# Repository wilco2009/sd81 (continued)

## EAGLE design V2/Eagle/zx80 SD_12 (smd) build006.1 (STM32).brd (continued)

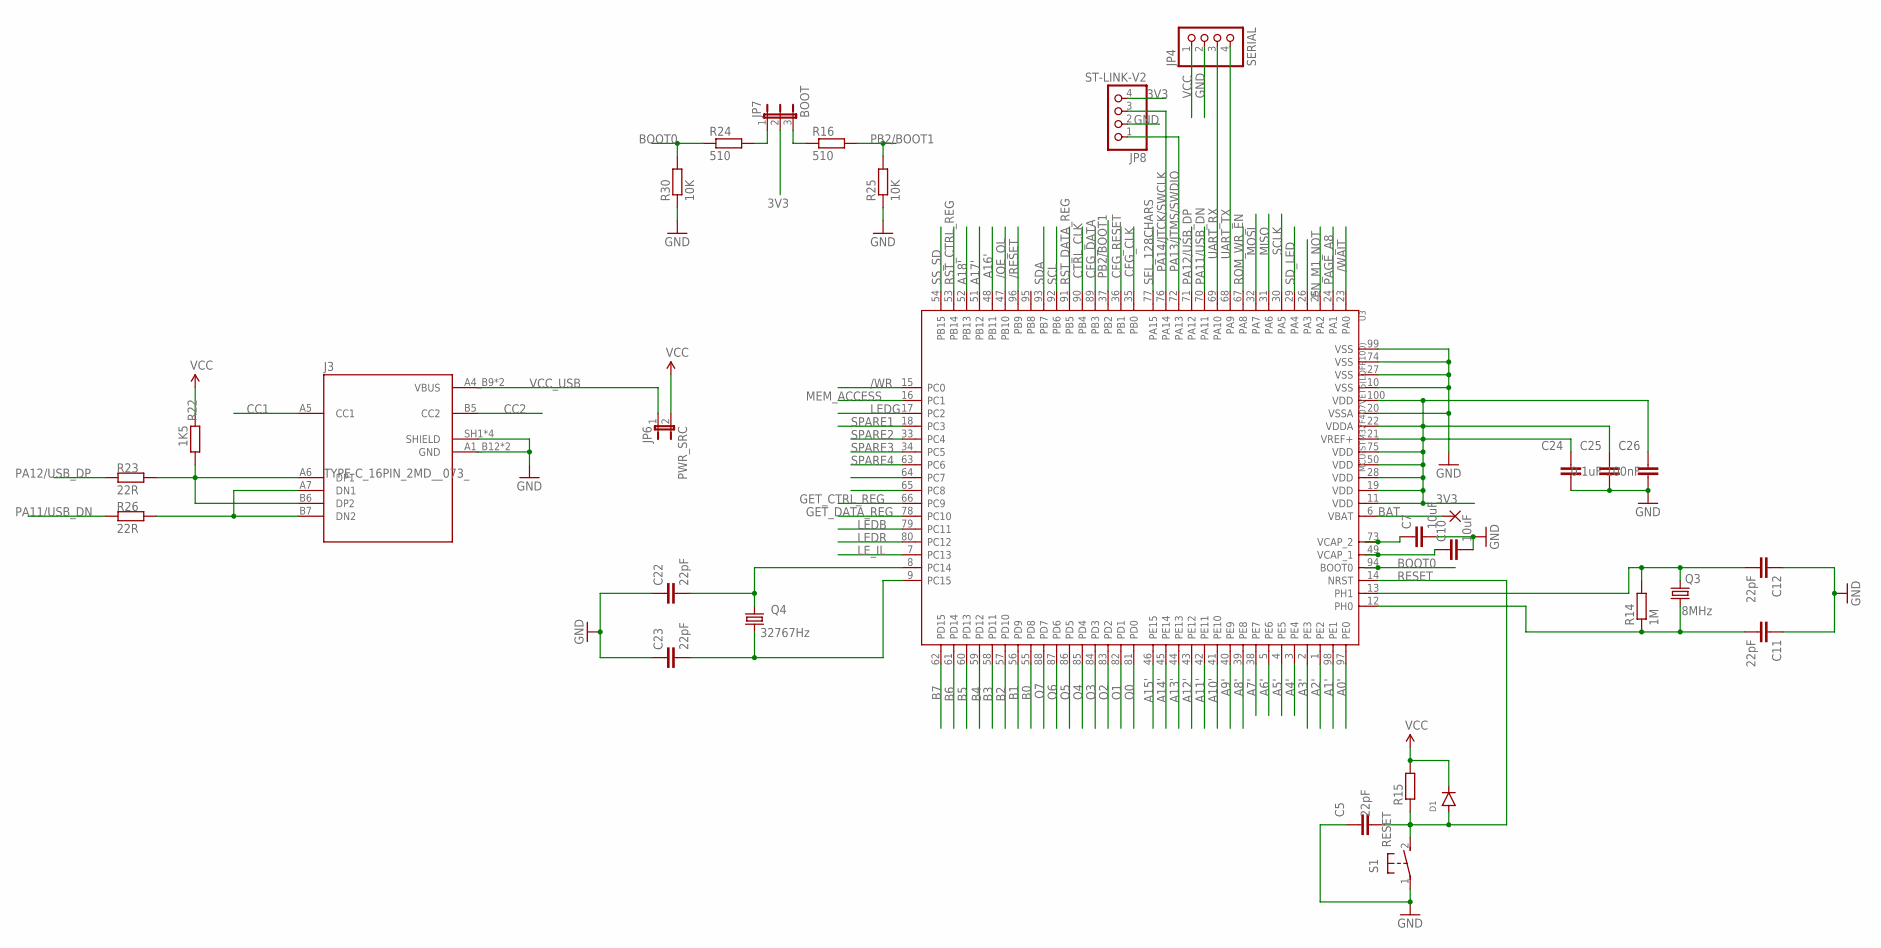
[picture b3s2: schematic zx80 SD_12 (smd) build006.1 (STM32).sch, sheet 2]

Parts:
BAT: 1,6/0,8
C5, C11, C12, C22, C23: 22pF; C0603
C7, C10: 10uF; C1206
C24, C25: 0.1uF; C0603
C26: 100nF; C0603
D1: DIODE-SOD123; SOD123
J3: TYPE-C_16PIN_2MD__073_; SHOUHAN_TYPE-C_16PIN_2MD__073_
JP4: SERIAL; 1X04
JP6: PWR_SRC; HDRV2W64P254_2X1_300X350X838B
JP7: BOOT; HDRV3W64P254_3X1_300X654X838B
JP8: ST-LINK-V2; 1X04
Q3: 8MHz; 3.2X2.5_KX-7
Q4: 32767Hz; 3.2X1.5
R14: 1M; R0603
R15: R0603
R16, R24: 510; R0603
R22: 1K5; R0603
R23, R26: 22R; R0603
R25, R30: 10K; R0603
S1: RESET; B3F-31XX
U3: MCU-STM32F407VET6(LQFP100); LQFP100-0.5-13.8X13.8MM

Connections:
3V3: C24.1, C25.1, C26.1, JP7.2, JP8.4, U3.11 (VDD), U3.19 (VDD), U3.21 (VREF+), U3.22 (VDDA), U3.28 (VDD), U3.50 (VDD), U3.75 (VDD), U3.100 (VDD); also elsewhere on the board
/OE_OL: U3.47 (PB10); also elsewhere on the board
/RESET: U3.96 (PB9); also elsewhere on the board
/WAIT: U3.23 (PA0); also elsewhere on the board
/WR: U3.15 (PC0); also elsewhere on the board
A0': U3.97 (PE0); also elsewhere on the board
A1': U3.98 (PE1); also elsewhere on the board
A2': U3.1 (PE2); also elsewhere on the board
A3': U3.2 (PE3); also elsewhere on the board
A4': U3.3 (PE4); also elsewhere on the board
A5': U3.4 (PE5); also elsewhere on the board
A6': U3.5 (PE6); also elsewhere on the board
A7': U3.38 (PE7); also elsewhere on the board
A8': U3.39 (PE8); also elsewhere on the board
A9': U3.40 (PE9); also elsewhere on the board
A10': U3.41 (PE10); also elsewhere on the board
A11': U3.42 (PE11); also elsewhere on the board
A12': U3.43 (PE12); also elsewhere on the board
A13': U3.44 (PE13); also elsewhere on the board
A14': U3.45 (PE14); also elsewhere on the board
A15': U3.46 (PE15); also elsewhere on the board
A16': U3.48 (PB11); also elsewhere on the board
A17': U3.51 (PB12); also elsewhere on the board
A18': U3.52 (PB13); also elsewhere on the board
B0: U3.55 (PD8); also elsewhere on the board
B1: U3.56 (PD9); also elsewhere on the board
B2: U3.57 (PD10); also elsewhere on the board
B3: U3.58 (PD11); also elsewhere on the board
B4: U3.59 (PD12); also elsewhere on the board
B5: U3.60 (PD13); also elsewhere on the board
B6: U3.61 (PD14); also elsewhere on the board
B7: U3.62 (PD15); also elsewhere on the board
BAT: BAT.1, U3.6 (VBAT)
BOOT0: R24.1, R30.2, U3.94 (BOOT0)
CC1: J3.A5 (CC1)
CC2: J3.B5 (CC2)
CFG_CLK: U3.35 (PB0); also elsewhere on the board
CFG_DATA: U3.89 (PB3); also elsewhere on the board
CFG_RESET: U3.36 (PB1); also elsewhere on the board
CTRL_CLK: U3.90 (PB4); also elsewhere on the board
EN_M1_NOT: U3.25 (PA2); also elsewhere on the board
GET_CTRL_REG: U3.66 (PC9); also elsewhere on the board
GET_DATA_REG: U3.78 (PC10); also elsewhere on the board
GND: C5.1, C7.2, C10.2, C11.1, C12.1, C22.1, C23.1, C24.2, C25.2, C26.2, J3.A1_B12 (GND), J3.B1_A12 (GND), J3.SH1 (SHIELD), J3.SH2 (SHIELD), J3.SH3 (SHIELD), J3.SH4 (SHIELD), JP4.2, JP8.2, R25.1, R30.1, S1.1, U3.10 (VSS), U3.20 (VSSA), U3.27 (VSS), U3.74 (VSS), U3.99 (VSS); also elsewhere on the board
LEDB: U3.79 (PC11); also elsewhere on the board
LEDG: U3.17 (PC2); also elsewhere on the board
LEDR: U3.80 (PC12); also elsewhere on the board
LE_IL: U3.7 (PC13); also elsewhere on the board
MEM_ACCESS: U3.16 (PC1); also elsewhere on the board
MISO: U3.31 (PA6); also elsewhere on the board
MOSI: U3.32 (PA7); also elsewhere on the board
unnamed: J3.A6 (DP1), J3.B6 (DP2), R22.1, R23.1
unnamed: C7.1, U3.73 (VCAP_2)
unnamed: J3.A7 (DN1), J3.B7 (DN2), R26.1
unnamed: C10.1, U3.49 (VCAP_1)
unnamed: C11.2, Q3.1, R14.1, U3.12 (PH0)
unnamed: C12.2, Q3.3 (2), R14.2, U3.13 (PH1)
unnamed: JP7.3, R16.1
unnamed: JP7.1, R24.2
unnamed: C22.2, Q4.2, U3.8 (PC14)
unnamed: C23.2, Q4.1, U3.9 (PC15)
O0: U3.81 (PD0); also elsewhere on the board
O1: U3.82 (PD1); also elsewhere on the board
O2: U3.83 (PD2); also elsewhere on the board
O3: U3.84 (PD3); also elsewhere on the board
O4: U3.85 (PD4); also elsewhere on the board
O5: U3.86 (PD5); also elsewhere on the board
O6: U3.87 (PD6); also elsewhere on the board
O7: U3.88 (PD7); also elsewhere on the board
PA11/USB_DN: R26.2, U3.70 (PA11)
PA12/USB_DP: R23.2, U3.71 (PA12)
PA13/JTMS/SWDIO: JP8.1, U3.72 (PA13)
PA14/JTCK/SWCLK: JP8.3, U3.76 (PA14)
PAGE_A8: U3.24 (PA1); also elsewhere on the board
PB2/BOOT1: R16.2, R25.2, U3.37 (PB2)
RESET: C5.2, D1.A, R15.1, S1.2 (S), U3.14 (NRST)
ROM_WR_EN: U3.67 (PA8); also elsewhere on the board
RST_CTRL_REG: U3.53 (PB14); also elsewhere on the board
RST_DATA_REG: U3.91 (PB5); also elsewhere on the board
SCL: U3.92 (PB6); also elsewhere on the board
SCLK: U3.30 (PA5); also elsewhere on the board
SDA: U3.93 (PB7); also elsewhere on the board
SD_LED: U3.29 (PA4); also elsewhere on the board
SEL_128CHARS: U3.77 (PA15); also elsewhere on the board
SPARE1: U3.18 (PC3); also elsewhere on the board
SPARE2: U3.33 (PC4); also elsewhere on the board
SPARE3: U3.34 (PC5); also elsewhere on the board
SPARE4: U3.63 (PC6); also elsewhere on the board
SS_SD: U3.54 (PB15); also elsewhere on the board
UART_RX: JP4.3, U3.69 (PA10)
UART_TX: JP4.4, U3.68 (PA9)
VCC: D1.C, JP4.1, JP6.2, R15.2, R22.2; also elsewhere on the board
VCC_USB: J3.A4_B9 (VBUS), J3.B4_A9 (VBUS), JP6.1

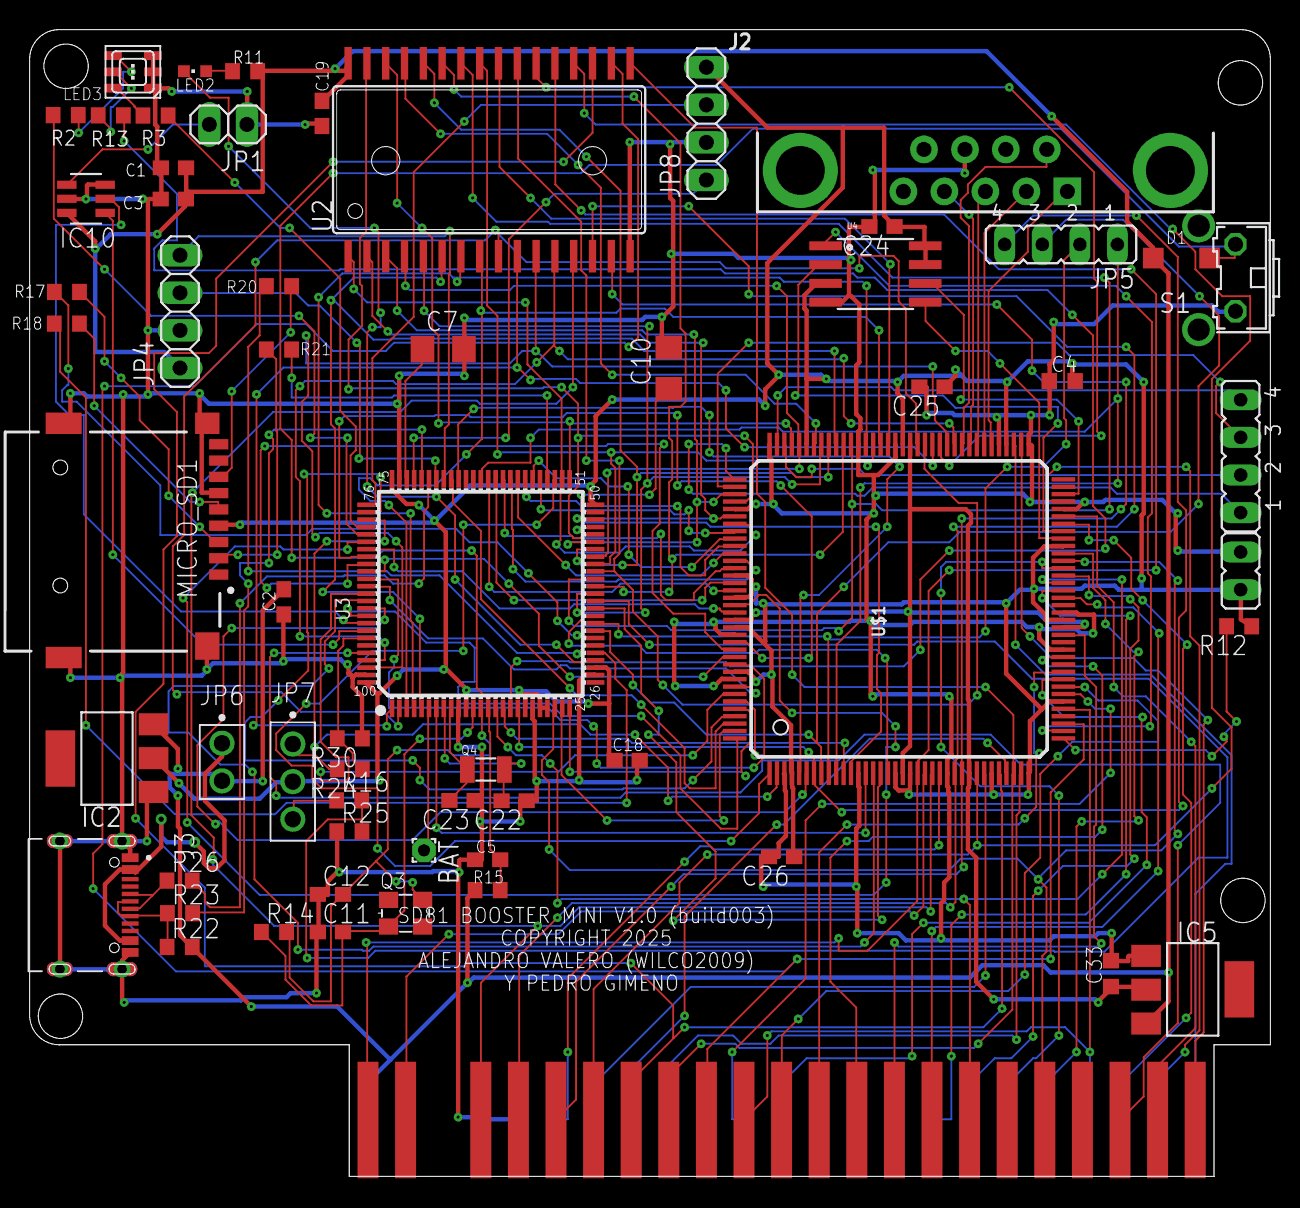
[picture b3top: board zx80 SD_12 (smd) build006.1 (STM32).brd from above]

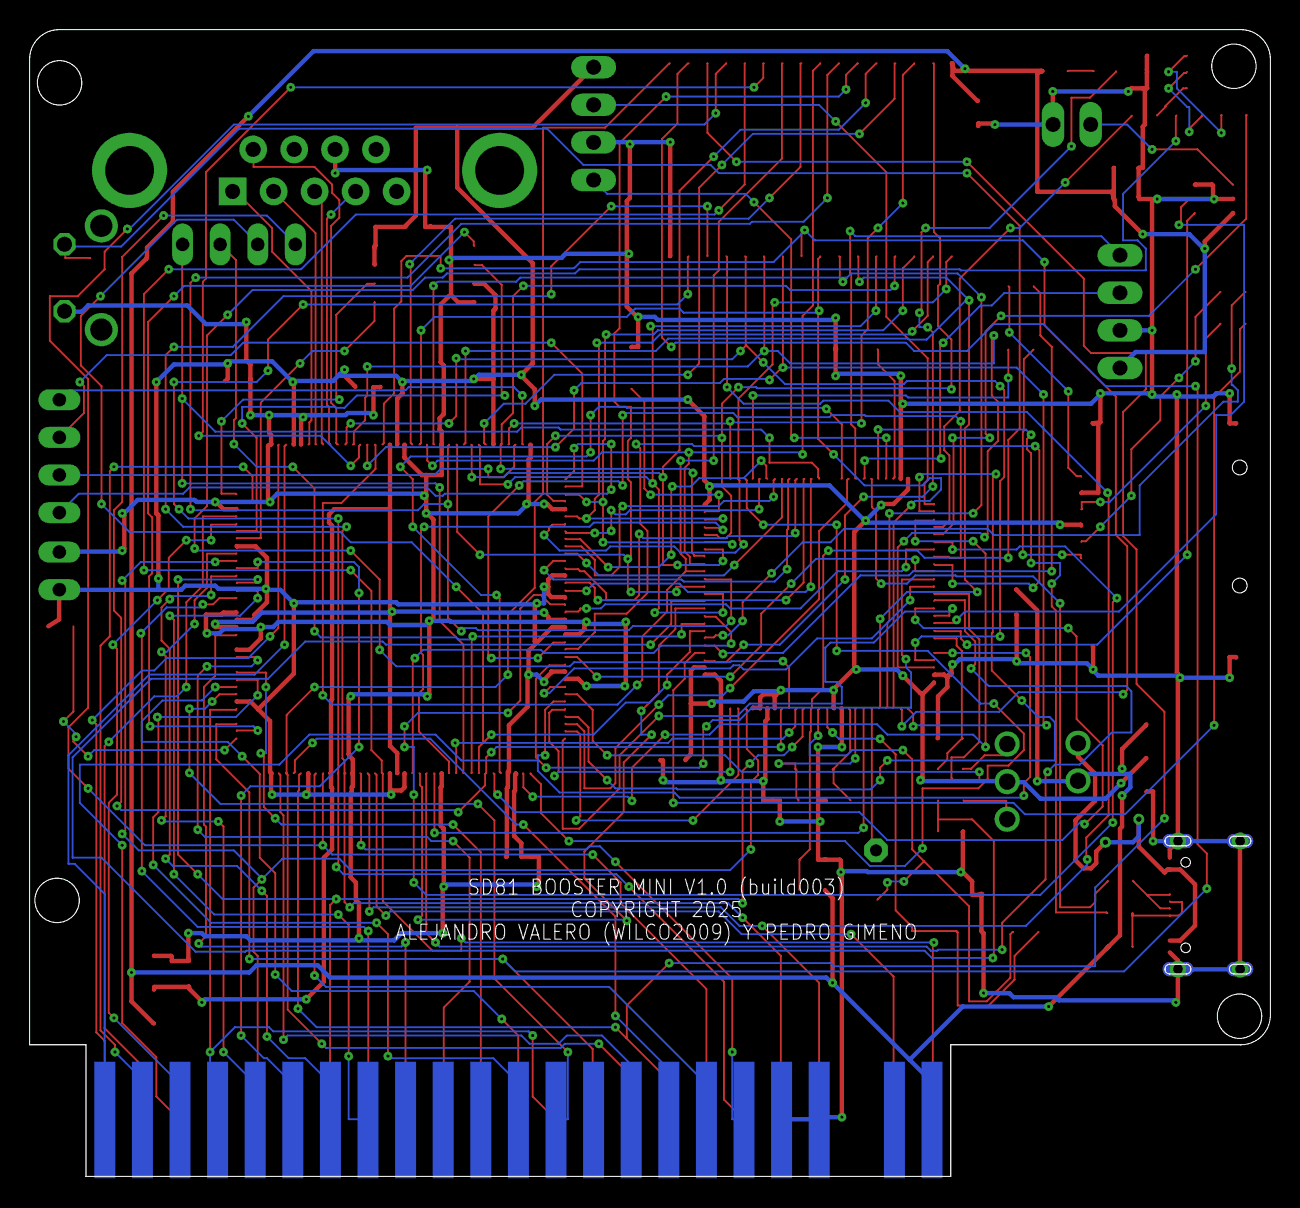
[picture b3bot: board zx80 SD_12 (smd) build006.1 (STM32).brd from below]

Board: 2 copper layers, 83.8 x 77.5 mm, 104 parts (22 on the bottom side), 152 nets.

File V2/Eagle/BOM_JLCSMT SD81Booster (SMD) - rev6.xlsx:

Comment | Designator | Footprint | JLCPCB Part #（optional）
100nF | C1 | C0603 | C14663
100nF | C2 | C0603 | C14663
10uF | C3 | C1206 | C19702
100nF | C4 | C0603 | C14663
22pF | C5 | C0603 | C1653
10uF | C6 | C1206 | C19702
10uF | C7 | C1206 | C19702
10uF | C10 | C1206 | C19702
22pF | C11 | C0603 | C1653
22pF | C12 | C0603 | C1653
100nF | C18 | C0603 | C14663
100nF | C19 | C0603 | C14663
22pF | C22 | C0603 | C1653
22pF | C23 | C0603 | C1653
100nF | C24 | C0603 | C14663
100nF | C25 | C0603 | C14663
100nF | C26 | C0603 | C14663
10uF | C33 | C1206 | C19702
1n4148 | D1 | SOD123 | C81598
1n5819 | D2 | SOD323-W | C191023
1n5819 | D4 | SOD323-W | C191023
REG1117 | IC2 | SOT223 | C6186
1,2V | IC5 | SOT223 | C347218
MCP4725 | IC10 | SOT-23-6_MC | C144198
JOYSTICK | J2 | DB9_MALE
TYPE-C_16PIN_2MD__073_ | J3 | SHOUHAN_TYPE-C_16PIN_2MD__073_ | C393939
SOUND | JP1 | 1X02
 | JP2 | 1X02
JTAG | JP3 | 1X04
SERIAL | JP4 | 1X04
RGB | JP5 | JP4
PS2 | JP6 | 1X02
BOOT | JP7 | HDRV3W64P254_3X1_300X654X838B
ST-LINK-V2 | JP8 | 1X04
SD | LED2 | CHIPLED_0805 | C2297
STATUS | LED3 | 3535-PLCC6 | C110402
TF-01A | MICRO_SD1 | TF-01A | C2889258
8MHz | Q3 | 3,2X2,5_KX-7 | C403948
32768Hz | Q4 | 3,2X1,5 | C32346
150 | R2 | R0603 | C22808
68 | R3 | R0603 | C27592
680 | R11 | R0603 | C17798
2K | R12 | R0603 | C22975
150 | R13 | R0603 | C22808
1M | R14 | R0603 | C22935
3k3 | R15 | R0603 | C22978
510 | R16 | R0603 | C23193
3k3 | R17 | R0603 | C22978
3k3 | R18 | R0603 | C22978
3k3 | R20 | R0603 | C22978
3k3 | R21 | R0603 | C22978
1K5 | R22 | R0603 | C22843
22R | R23 | R0603 | C23345
510 | R24 | R0603 | C23193
10K | R25 | R0603 | C25804
22R | R26 | R0603 | C23345
10K | R30 | R0603 | C25804
RESET | S1 | B3F-31XX
XC6SLX9-2TQG144C | U$1 | TQ144 | C27408
AS6C4008 | U2 | SOP32-5 | C2952831
MCU-STM32F407VET6(LQFP100) | U3 | LQFP100-0,5-13,8X13,8MM | C28730
FLASH-SPI-25XX | U4 | SO08-EIAJ | C97521

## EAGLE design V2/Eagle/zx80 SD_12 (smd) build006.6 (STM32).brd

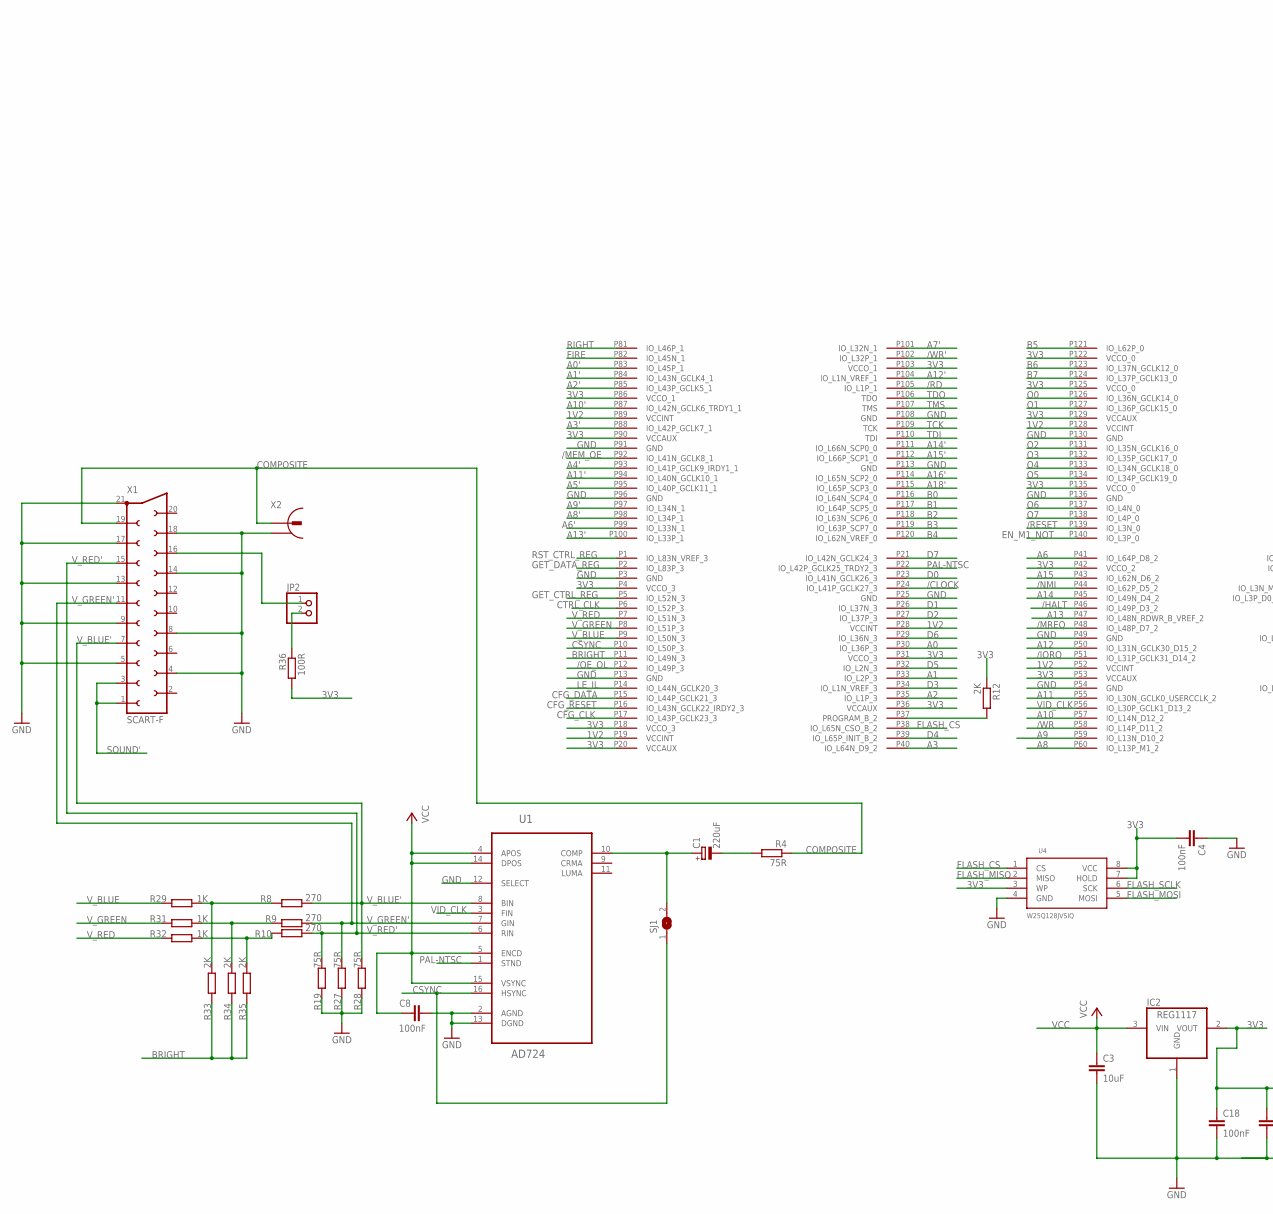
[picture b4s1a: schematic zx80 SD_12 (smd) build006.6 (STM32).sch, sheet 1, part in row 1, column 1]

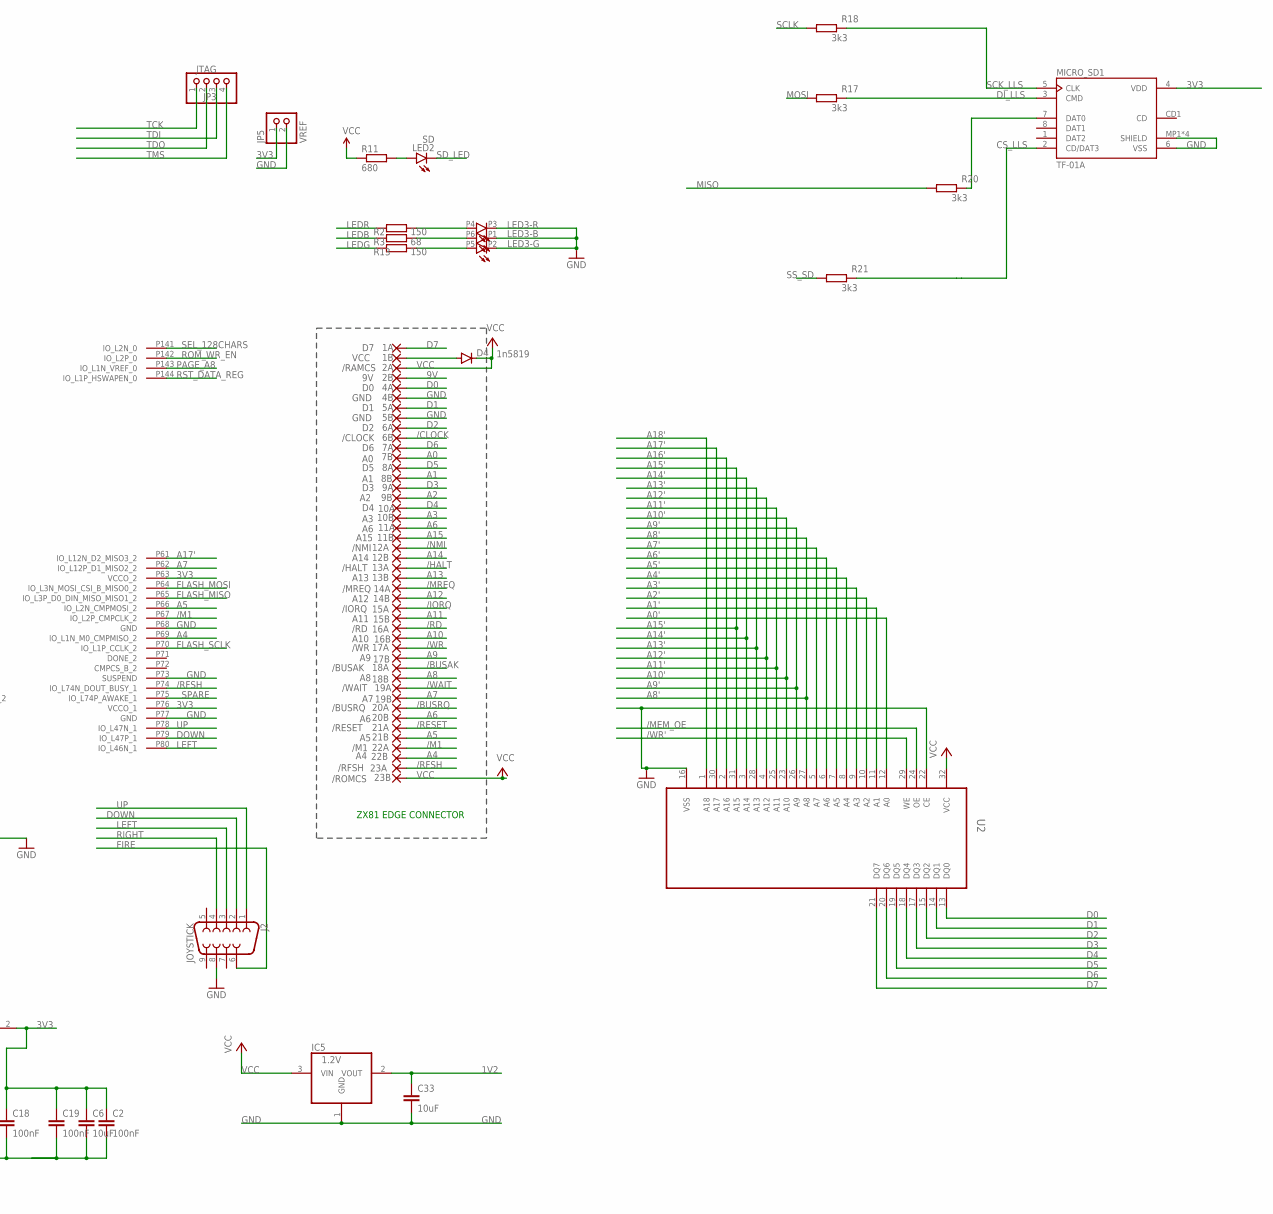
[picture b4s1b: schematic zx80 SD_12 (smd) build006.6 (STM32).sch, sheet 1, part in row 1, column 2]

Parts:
1A: D7; EDGEPIN
1B: VCC; EDGEPIN
2A: /RAMCS; EDGEPIN
2B: 9V; EDGEPIN
4A: D0; EDGEPIN
4B, 5B: GND; EDGEPIN
5A: D1; EDGEPIN
6A: D2; EDGEPIN
6B: /CLOCK; EDGEPIN
7A: D6; EDGEPIN
7B: A0; EDGEPIN
8A: D5; EDGEPIN
8B: A1; EDGEPIN
9A: D3; EDGEPIN
9B: A2; EDGEPIN
10A: D4; EDGEPIN
10B: A3; EDGEPIN
11A, 20B: A6; EDGEPIN
11B: A15; EDGEPIN
12A: /NMI; EDGEPIN
12B: A14; EDGEPIN
13A: /HALT; EDGEPIN
13B: A13; EDGEPIN
14A: /MREQ; EDGEPIN
14B: A12; EDGEPIN
15A: /IORQ; EDGEPIN
15B: A11; EDGEPIN
16A: /RD; EDGEPIN
16B: A10; EDGEPIN
17A: /WR; EDGEPIN
17B: A9; EDGEPIN
18A: /BUSAK; EDGEPIN
18B: A8; EDGEPIN
19A: /WAIT; EDGEPIN
19B: A7; EDGEPIN
20A: /BUSRQ; EDGEPIN
21A: /RESET; EDGEPIN
21B: A5; EDGEPIN
22A: /M1; EDGEPIN
22B: A4; EDGEPIN
23A: /RFSH; EDGEPIN
23B: /ROMCS; EDGEPIN
C1: 220uF; UD-6,3X7,7_NICHICON
C2, C4, C18, C19: 100nF; C0603
C3, C6, C33: 10uF; C0603
C8: 100nF; C0603K
D4: 1n5819; SOD323-W
IC2: REG1117; SOT223
IC5: 1.2V; SOT223
J2: JOYSTICK; DB9_MALE
JP2: PINHD-1X2; 1X02
JP3: JTAG; 1X04
JP5: VREF; 1X02
LED2: SD; CHIPLED_0805
LED3: STATUS; 3535-PLCC6
MICRO_SD1: TF-01A
R2, R13: 150; R0603
R3: 68; R0603
R4, R19, R27, R28: 75R; R0603
R8, R9, R10: 270; R0603
R11: 680; R0603
R12, R33, R34, R35: 2K; R0402
R17, R18, R20, R21: 3k3; R0603
R29, R31, R32: 1K; R0402
R36: 100R; R0603
SJ1: SJ
U1: AD724; SOIC127P1032X265-16N
U2: AS6C4008; SOP32-5
U4: W25Q128JVSIQ; SO08-EIAJ
U6: XC6SLX9-2TQG144C; TQ144
X1: SCART-F
X2: CON-CONRAD_736880-2P; 3P

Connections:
1V2: C33.1, IC5.2 (VOUT), U6.P19 (VCCINT), U6.P28 (VCCINT), U6.P52 (VCCINT), U6.P89 (VCCINT), U6.P128 (VCCINT)
3V3: C2.1, C4.2, C6.1, C18.1, C19.1, IC2.2 (VOUT), JP5.1, MICRO_SD1.4 (VDD), R12.1, R36.2, U4.3 (WP), U4.7 (HOLD), U4.8 (VCC), U6.P4 (VCCO_3), U6.P18 (VCCO_3), U6.P20 (VCCAUX), U6.P31 (VCCO_3), U6.P36 (VCCAUX), U6.P42 (VCCO_2), U6.P53 (VCCAUX), U6.P63 (VCCO_2), U6.P76 (VCCO_1), U6.P86 (VCCO_1), U6.P90 (VCCAUX), U6.P103 (VCCO_1), U6.P122 (VCCO_0), U6.P125 (VCCO_0), U6.P129 (VCCAUX), U6.P135 (VCCO_0); also elsewhere on the board
9V: 2B.1
/BUSAK: 18A.1
/BUSRQ: 20A.1
/CLOCK: 6B.1, U6.P24 (IO_L41P_GCLK27_3)
/HALT: 13A.1, U6.P46 (IO_L49P_D3_2)
/IORQ: 15A.1, U6.P51 (IO_L31P_GCLK31_D14_2)
/M1: 22A.1, U6.P67 (IO_L2P_CMPCLK_2)
/MEM_OE: U2.24 (OE), U6.P92 (IO_L41N_GCLK8_1)
/MREQ: 14A.1, U6.P48 (IO_L48P_D7_2)
/NMI: 12A.1, U6.P44 (IO_L62P_D5_2)
/OE_OL: U6.P12 (IO_L49P_3); also elsewhere on the board
/RD: 16A.1, U6.P105 (IO_L1P_1)
/RESET: 21A.1, U6.P139 (IO_L3N_0); also elsewhere on the board
/RFSH: 23A.1, U6.P74 (IO_L74N_DOUT_BUSY_1)
/WAIT: 19A.1; also elsewhere on the board
/WR: 17A.1, U6.P58 (IO_L14P_D11_2)
/WR': U2.29 (WE), U6.P102 (IO_L32P_1); also elsewhere on the board
A0: 7B.1, U6.P30 (IO_L36P_3)
A0': U2.12 (A0), U6.P83 (IO_L45P_1); also elsewhere on the board
A1: 8B.1, U6.P33 (IO_L2P_3)
A1': U2.11 (A1), U6.P84 (IO_L43N_GCLK4_1); also elsewhere on the board
A2: 9B.1, U6.P35 (IO_L1P_3)
A2': U2.10 (A2), U6.P85 (IO_L43P_GCLK5_1); also elsewhere on the board
A3: 10B.1, U6.P40 (IO_L64N_D9_2)
A3': U2.9 (A3), U6.P88 (IO_L42P_GCLK7_1); also elsewhere on the board
A4: 22B.1, U6.P69 (IO_L1N_M0_CMPMISO_2)
A4': U2.8 (A4), U6.P93 (IO_L41P_GCLK9_IRDY1_1); also elsewhere on the board
A5: 21B.1, U6.P66 (IO_L2N_CMPMOSI_2)
A5': U2.7 (A5), U6.P95 (IO_L40P_GCLK11_1); also elsewhere on the board
A6: 11A.1, 20B.1, U6.P41 (IO_L64P_D8_2)
A6': U2.6 (A6), U6.P99 (IO_L33N_1); also elsewhere on the board
A7: 19B.1, U6.P62 (IO_L12P_D1_MISO2_2)
A7': U2.5 (A7), U6.P101 (IO_L32N_1); also elsewhere on the board
A8: 18B.1, U6.P60 (IO_L13P_M1_2)
A8': U2.27 (A8), U6.P98 (IO_L34P_1); also elsewhere on the board
A9: 17B.1, U6.P59 (IO_L13N_D10_2)
A9': U2.26 (A9), U6.P97 (IO_L34N_1); also elsewhere on the board
A10: 16B.1, U6.P57 (IO_L14N_D12_2)
A10': U2.23 (A10), U6.P87 (IO_L42N_GCLK6_TRDY1_1); also elsewhere on the board
A11: 15B.1, U6.P55 (IO_L30N_GCLK0_USERCCLK_2)
A11': U2.25 (A11), U6.P94 (IO_L40N_GCLK10_1); also elsewhere on the board
A12: 14B.1, U6.P50 (IO_L31N_GCLK30_D15_2)
A12': U2.4 (A12), U6.P104 (IO_L1N_VREF_1); also elsewhere on the board
A13: 13B.1, U6.P47 (IO_L48N_RDWR_B_VREF_2)
A13': U2.28 (A13), U6.P100 (IO_L33P_1); also elsewhere on the board
A14: 12B.1, U6.P45 (IO_L49N_D4_2)
A14': U2.3 (A14), U6.P111 (IO_L66N_SCP0_0); also elsewhere on the board
A15: 11B.1, U6.P43 (IO_L62N_D6_2)
A15': U2.31 (A15), U6.P112 (IO_L66P_SCP1_0); also elsewhere on the board
A16': U2.2 (A16), U6.P114 (IO_L65N_SCP2_0); also elsewhere on the board
A17': U2.30 (A17), U6.P61 (IO_L12N_D2_MISO3_2); also elsewhere on the board
A18': U2.1 (A18), U6.P115 (IO_L65P_SCP3_0); also elsewhere on the board
B0: U6.P116 (IO_L64N_SCP4_0); also elsewhere on the board
B1: U6.P117 (IO_L64P_SCP5_0); also elsewhere on the board
B2: U6.P118 (IO_L63N_SCP6_0); also elsewhere on the board
B3: U6.P119 (IO_L63P_SCP7_0); also elsewhere on the board
B4: U6.P120 (IO_L62N_VREF_0); also elsewhere on the board
B5: U6.P121 (IO_L62P_0); also elsewhere on the board
B6: U6.P123 (IO_L37N_GCLK12_0); also elsewhere on the board
B7: U6.P124 (IO_L37P_GCLK13_0); also elsewhere on the board
BRIGHT: R33.1, R34.1, R35.1, U6.P11 (IO_L49N_3)
CFG_CLK: U6.P17 (IO_L43P_GCLK23_3); also elsewhere on the board
CFG_DATA: U6.P15 (IO_L44P_GCLK21_3); also elsewhere on the board
CFG_RESET: U6.P16 (IO_L43N_GCLK22_IRDY2_3); also elsewhere on the board
COMPOSITE: R4.1, X1.19, X2.2 (1)
CSYNC: SJ1.1, U1.16 (HSYNC), U6.P10 (IO_L50P_3)
CS_LLS: MICRO_SD1.2 (CD/DAT3), R21.2
CTRL_CLK: U6.P6 (IO_L52P_3); also elsewhere on the board
D0: 4A.1, U2.13 (DQ0), U6.P23 (IO_L41N_GCLK26_3)
D1: 5A.1, U2.14 (DQ1), U6.P26 (IO_L37N_3)
D2: 6A.1, U2.15 (DQ2), U6.P27 (IO_L37P_3)
D3: 9A.1, U2.17 (DQ3), U6.P34 (IO_L1N_VREF_3)
D4: 10A.1, U2.18 (DQ4), U6.P39 (IO_L65P_INIT_B_2)
D5: 8A.1, U2.19 (DQ5), U6.P32 (IO_L2N_3)
D6: 7A.1, U2.20 (DQ6), U6.P29 (IO_L36N_3)
D7: 1A.1, U2.21 (DQ7), U6.P21 (IO_L42N_GCLK24_3)
DI_LLS: MICRO_SD1.3 (CMD), R17.2
DOWN: J2.2, U6.P79 (IO_L47P_1)
EN_M1_NOT: U6.P140 (IO_L3P_0); also elsewhere on the board
FIRE: J2.6, U6.P82 (IO_L45N_1)
FLASH_CS: U4.1 (CS), U6.P38 (IO_L65N_CSO_B_2)
FLASH_MISO: U4.2 (MISO), U6.P65 (IO_L3P_D0_DIN_MISO_MISO1_2)
FLASH_MOSI: U4.5 (MOSI), U6.P64 (IO_L3N_MOSI_CSI_B_MISO0_2)
FLASH_SCLK: U4.6 (SCK), U6.P70 (IO_L1P_CCLK_2)
GET_CTRL_REG: U6.P5 (IO_L52N_3); also elsewhere on the board
GET_DATA_REG: U6.P2 (IO_L83P_3); also elsewhere on the board
GND: 4B.1, 5B.1, C2.2, C3.2, C4.1, C6.2, C8.1, C18.2, C19.2, C33.2, IC2.1 (GND), IC5.1 (GND), J2.8, JP5.2, LED3.P1 (C), LED3.P2 (C), LED3.P3 (C), MICRO_SD1.6 (VSS), MICRO_SD1.MP1 (SHIELD), MICRO_SD1.MP2 (SHIELD), MICRO_SD1.MP3 (SHIELD), MICRO_SD1.MP4 (SHIELD), R19.2, R27.2, R28.2, U1.2 (AGND), U1.12 (SELECT), U1.13 (DGND), U2.16 (VSS), U2.22 (CE), U4.4 (GND), U6.P3 (GND), U6.P13 (GND), U6.P25 (GND), U6.P49 (GND), U6.P54 (GND), U6.P68 (GND), U6.P73 (SUSPEND), U6.P77 (GND), U6.P91 (GND), U6.P96 (GND), U6.P108 (GND), U6.P113 (GND), U6.P130 (GND), U6.P136 (GND), X1.4, X1.5, X1.8, X1.9, X1.13, X1.14, X1.17, X1.18, X1.21, X2.1 (2); also elsewhere on the board
LEDB: R3.1; also elsewhere on the board
LEDG: R13.1; also elsewhere on the board
LEDR: R2.1; also elsewhere on the board
LEFT: J2.3, U6.P80 (IO_L46N_1)
LE_IL: U6.P14 (IO_L44N_GCLK20_3); also elsewhere on the board
MISO: R20.1; also elsewhere on the board
MOSI: R17.1; also elsewhere on the board
unnamed: C1.+, SJ1.2, U1.10 (COMP)
unnamed: MICRO_SD1.7 (DAT0), R20.2
unnamed: 1B.1, D4.A
unnamed: C1.-, R4.2
unnamed: R12.2, U6.P37 (PROGRAM_B_2)
unnamed: LED2.A, R11.2
unnamed: JP2.1, X1.16
unnamed: LED3.P4 (A), R2.2
unnamed: LED3.P6 (A), R3.2
unnamed: LED3.P5 (A), R13.2
unnamed: JP2.2, R36.1
unnamed: R8.2, R29.2, R33.2
unnamed: R9.2, R31.2, R34.2
unnamed: R10.2, R32.2, R35.2
O0: U6.P126 (IO_L36N_GCLK14_0); also elsewhere on the board
O1: U6.P127 (IO_L36P_GCLK15_0); also elsewhere on the board
O2: U6.P131 (IO_L35N_GCLK16_0); also elsewhere on the board
O3: U6.P132 (IO_L35P_GCLK17_0); also elsewhere on the board
O4: U6.P133 (IO_L34N_GCLK18_0); also elsewhere on the board
O5: U6.P134 (IO_L34P_GCLK19_0); also elsewhere on the board
O6: U6.P137 (IO_L4N_0); also elsewhere on the board
O7: U6.P138 (IO_L4P_0); also elsewhere on the board
PAGE_A8: U6.P143 (IO_L1N_VREF_0); also elsewhere on the board
PAL-NTSC: U1.1 (STND), U6.P22 (IO_L42P_GCLK25_TRDY2_3)
RIGHT: J2.4, U6.P81 (IO_L46P_1)
ROM_WR_EN: U6.P142 (IO_L2P_0); also elsewhere on the board
RST_CTRL_REG: U6.P1 (IO_L83N_VREF_3); also elsewhere on the board
RST_DATA_REG: U6.P144 (IO_L1P_HSWAPEN_0); also elsewhere on the board
SCK_LLS: MICRO_SD1.5 (CLK), R18.2
SCLK: R18.1; also elsewhere on the board
SD_LED: LED2.C; also elsewhere on the board
SEL_128CHARS: U6.P141 (IO_L2N_0); also elsewhere on the board
SOUND': X1.1, X1.3; also elsewhere on the board
SPARE: U6.P75 (IO_L74P_AWAKE_1)
SS_SD: R21.1; also elsewhere on the board
TCK: JP3.1, U6.P109 (TCK)
TDI: JP3.3, U6.P110 (TDI)
TDO: JP3.2, U6.P106 (TDO)
TMS: JP3.4, U6.P107 (TMS)
UP: J2.1, U6.P78 (IO_L47N_1)
VCC: 2A.1, 23B.1, C3.1, C8.2, D4.C, IC2.3 (VIN), IC5.3 (VIN), R11.1, U1.4 (APOS), U1.5 (ENCD), U1.14 (DPOS), U1.15 (VSYNC), U2.32 (VCC); also elsewhere on the board
VID_CLK: U1.3 (FIN), U6.P56 (IO_L30P_GCLK1_D13_2)
V_BLUE: R29.1, U6.P9 (IO_L50N_3)
V_BLUE': R8.1, R28.1, U1.8 (BIN), X1.7
V_GREEN: R31.1, U6.P8 (IO_L51P_3)
V_GREEN': R9.1, R27.1, U1.7 (GIN), X1.11
V_RED: R32.1, U6.P7 (IO_L51N_3)
V_RED': R10.1, R19.1, U1.6 (RIN), X1.15

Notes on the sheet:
ZX81 EDGE CONNECTOR
